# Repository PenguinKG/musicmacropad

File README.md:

# PenguinK's Music Macro Pad
Music Macro Pad project for Hack Club's Blueprint

### Inspiration

I wanted to create a macropad for quickly controlling my music, skipping tracks, changing the volume or muting.

### Challenges

This was my first time using KiCAD and Fusion360. I struggled a bit creating the case, understanding QMK and with the implementation of an encoder and an OLED screen. But, in the end, I'm proud of how it turned out.

### Specifications

BOM (https://docs.google.com/spreadsheets/d/1hUth15_CIp9PDY0lxdcaeFA97FQI-jCMW6N-8YT37j8/edit?usp=sharing):
- 3x Cherry MX Switches
- 1x EC11 Rotary Encoder
- 1x 0.91" 128x32 OLED Display
- 5x M3x16mm screws
- 4x Blank DSA Keycaps
- 1x XIAO RP2040
- 1x Case (2 Printed parts and a printed knob)

Firmware:
- QMK

Schematic            |  PCB         |   Case
:-------------------------:|:-------------------------:|:-------------------------:|
 |  |

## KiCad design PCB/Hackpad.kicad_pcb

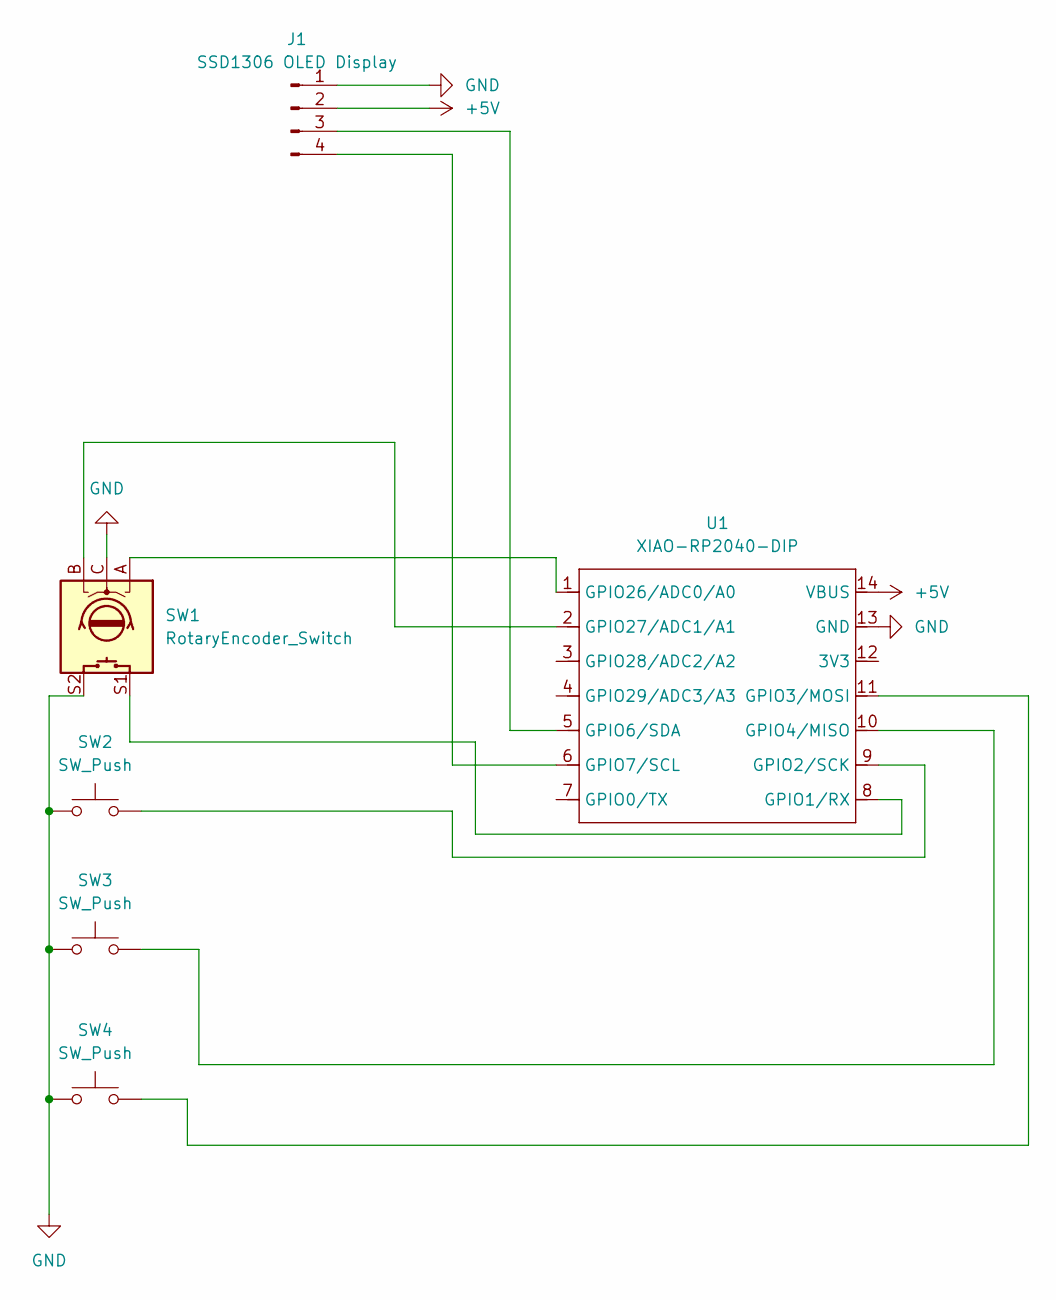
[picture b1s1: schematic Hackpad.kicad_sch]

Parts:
J1: SSD1306 OLED Display; SSD1306-0.91-OLED-4pin-128x32
SW1: RotaryEncoder_Switch; RotaryEncoder_Alps_EC11E-Switch_Vertical_H20mm
SW2, SW3, SW4: SW_Push; SW_Cherry_MX_1.00u_PCB
U1: XIAO-RP2040-DIP

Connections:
+5V: J1.2, U1.14 (VBUS)
GND: J1.1, SW1.C, SW1.S2, SW2.1, SW3.1, SW4.1, U1.13 (GND)
unnamed: J1.3, U1.5 (GPIO6/SDA)
unnamed: J1.4, U1.6 (GPIO7/SCL)
unnamed: SW1.S1, U1.8 (GPIO1/RX)
unnamed: SW2.2, U1.9 (GPIO2/SCK)
unnamed: SW4.2, U1.11 (GPIO3/MOSI)
unnamed: SW3.2, U1.10 (GPIO4/MISO)
unnamed: SW1.A, U1.1 (GPIO26/ADC0/A0)
unnamed: SW1.B, U1.2 (GPIO27/ADC1/A1)

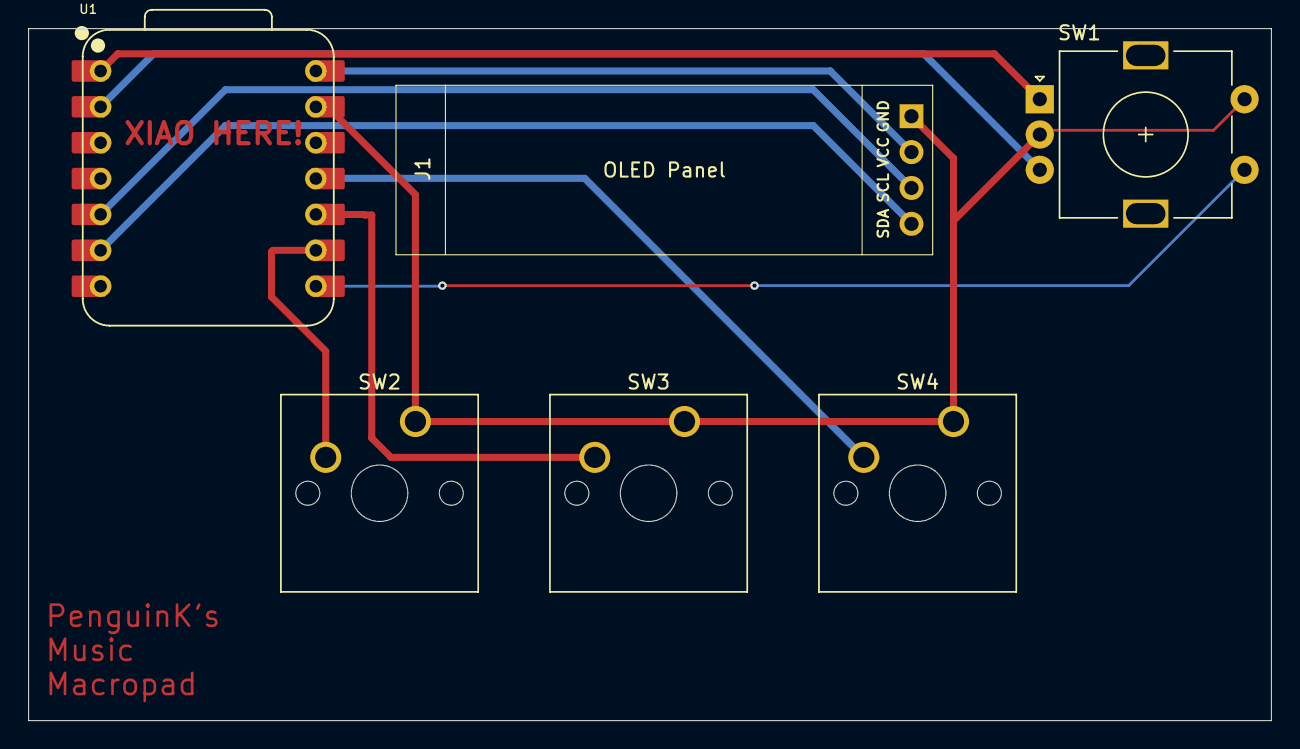
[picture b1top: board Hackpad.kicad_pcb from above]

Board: 2 copper layers, 88.0 x 49.0 mm, 6 parts (0 on the bottom side), 10 nets.

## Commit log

2025-12-06 Add Assets
2025-12-06 Add CAD
2025-12-06 Add Firmware
2025-12-06 Add PCB
2025-12-06 Update PCB
2025-12-08 Added the BOM.csv linked in the README
2026-02-28 Initial plan
